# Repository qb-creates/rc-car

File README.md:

# RC Car Project
This project is a custom-built remote-controlled (RC) car, designed from the ground up with custom electronics, PCB design, and embedded firmware for both the car and its remote.

- Project Video (YouTube): https://youtu.be/qdBbDeDglmY
- Bidirectional Motor Driver (H-Bridge): https://en.wikipedia.org/wiki/H-bridge
- Steering Servo PWM Control: https://en.wikipedia.org/wiki/Servo_control
- nRF24L01 Wireless Transceiver Module: https://www.instructables.com/NRF24L01-Tutorial-Arduino-Wireless-Communication/

<div align="center">
	
</div>

## Table of Contents
1. [Software Used](#software)
2. [Drive and Steering Control Circuit](#driveandsteeringcircuit)
    - [RF Receiver](#rfreceiver)
    - [Steering Servo Control](#steering)
    - [Drive Motor Control](#drivemotor)
    - [Power Consumption](#powerconsumption)
    - [Charging Notes](#carcharging)
    - [Parts List](#carpartslist)
    - [Schematics](#carschematics)
    - [PCB Images](#carpcbimages)
3. [Remote Control Circuit](#remotecontrolcircuit)
    - [RF Transmitter](#rftransmitter)
    - [Control Input Processing](#controlinputprocessing)
        - [Throttle Input (Left Analog Stick)](#throttleprocessing)
        - [Steering Input (Right Analog Stick)](#steeringprocessing)
    - [Charging Notes](#remotecharging)
    - [Parts List](#remotepartslist)
    - [Schematics](#remoteschematics)
    - [PCB Images](#remotepcbimages)
4. [Pin Mapping](#pinmapping)
    - [Car Controller (ATmega164A)](#carpinmapping)
    - [Remote Controller (ATmega164A)](#remotepinmapping)
5. [STL Viewer](#stlviewer)
    - [Car Mechanical Mounts STL](#carmechanicalmountsstl)
    - [Controller Housing STL](#controllerhousingstl)

## 1. Software Used
- VSCode with PlatformIO extension: https://docs.platformio.org/en/latest/what-is-platformio.html
- AVRDUDE (Flash Uploader): https://github.com/avrdudes/avrdude
- KiCad (PCB Design): https://www.kicad.org
- Tinkercad (Controller and parts Design): https://www.tinkercad.com/

## 2. Drive and Steering Control Circuit
This board is the car's real-time control core. It receives wireless throttle/steering commands from the handheld transmitter, converts steering targets into stable hardware PWM for the MG90S servo, and drives the rear motor through a protected H-bridge path with direction dead-time and command deadbands for smoother behavior. The result is a compact control system designed for responsive handling, predictable failsafe behavior, and reliable power delivery under changing load.

<div align="center">
 <table>
     <tr>
         <td></td>
         <td></td>
     </tr>
     <tr>
         <td></td>
         <td></td>
     </tr>
 </table>
</div>

### RF Receiver
The car uses an nRF24L01+ module with the RF24 library over SPI to receive drive and steering commands from the handheld controller. In firmware, the radio object is created as `RF24 radio(CE_PIN, CSN_PIN)` with CE on PB0 and CSN on PB1.

The RF stack is configured in `configureRFRadio()` with:

- `radio.begin()` hardware check (halts if radio is not detected)
- `radio.setPALevel(RF24_PA_LOW)` to reduce TX power/current
- `radio.enableDynamicPayloads()`
- `radio.setAutoAck(false)`
- Pipe/address setup using `"jag-1"` and `"jag-2"`
- `radio.startListening()` so this node stays in RX mode

An important part of the RF path is Timer0 timing configuration. Because this firmware includes `#include <RF24.h>`, the RF24 stack depends on `millis()`/`micros()` timing for operations such as CE pulse timing, transmit timing windows, retry timing, and transaction spacing.

The RF24 library itself does not directly configure Timer0. Instead, those timing primitives are provided by the Arduino core (`millis()`/`micros()`), and the project sets Timer0 for a 50 us timing base:

```cpp
TCCR0A = (1 << COM0B1) | (1 << WGM01) | (1 << WGM00);
TCCR0B = (1 << WGM02) | (1 << CS01); // prescaler = 8
OCR0A = 49;
```

At 8 MHz CPU clock with prescaler 8:

- Timer clock = 8 MHz / 8 = 1 MHz
- Timer tick = 1 us
- Period = (49 + 1) x 1 us = 50 us

So the Timer0 event period is 50 us (20 kHz). Timer0 is intentionally kept running at this rate so the `millis()`/`micros()` time base used by RF24 remains available and stable.

The receiver expects a `MotorControlPayload` packet with two fields:

- `int16_t ocrMotor` for signed throttle/drive command
- `uint16_t ocrSteering` for servo pulse width command in microseconds

This payload is 4 bytes total (`2 + 2`), and after reception the car firmware applies it directly:

- `OCR1B = payload.ocrSteering` for steering position
- `payload.ocrMotor` drives H-bridge direction/speed logic with a deadband of -15 to +15

Reliability/safety behavior tied to RF reception:

- On first valid packet, watchdog is enabled (`WDTO_2S`)
- Each additional valid packet resets the watchdog
- If RF packets stop arriving, watchdog timeout forces a reset/failsafe

### Steering Servo Control
Steering is driven by an MG90S servo using Timer1 hardware PWM on OC1B (PD4). The car firmware configures Timer1 in Fast PWM mode 14 with ICR1 as TOP, prescaler = 8, and ICR1 = 20000. With an 8 MHz clock, that gives a 1 us timer tick and about a 50 Hz control period (20 ms), which matches standard hobby servo timing.

The commanded steering pulse is written directly to OCR1B. Steering values are transmitted as absolute pulse widths in microseconds. Instead of assuming a fixed joystick center, the controller now supports calibration by entering measured joystick potentiometer voltages for minimum, maximum, and center. Those measured values are used to map ADC input to the steering pulse range and produce a more accurate neutral point (typically near 1900 us). On the car side, OCR1B is updated from the payload each loop:

- Neutral: calibrated from measured joystick center voltage (typically ~1900 us)
- Left/Right command range: ~1520 us to ~2280 us
- PWM period: ~20 ms (50 Hz)
- Steering deadzone: +/-90 us around calibrated center snaps to neutral to reduce twitch

This keeps steering response deterministic because the servo waveform is generated in hardware (Timer1), not by software toggling.

### Drive Motor Control
The drive motor uses a discrete H-bridge driven by a hybrid approach: latch lines select direction, while PWM is generated in software via Timer2 interrupts.

H-bridge signal assignment:

- PC0: Forward latch
- PC1: Forward PWM
- PC2: Reverse latch
- PC3: Reverse PWM

Timer2 is configured for Fast PWM with OCR2A as TOP. With OCR2A = 199 and prescaler = 8 at 8 MHz, PWM frequency is about 5 kHz. Instead of using OC2A/OC2B output pins directly, compare interrupts are used:

- TIMER2_COMPA_vect sets the active direction PWM pin high (PC1 for forward or PC3 for reverse)
- TIMER2_COMPB_vect clears that same active pin low

This effectively creates direction-dependent PWM on one of two output pins while the opposite side remains off.

Direction changes are intentionally staged to protect the bridge and drivetrain:

1. Disable Timer2 PWM (stop switching)
2. Force all H-bridge outputs low
3. Wait 150 ms dead-time
4. Assert new direction latch (PC0 forward or PC2 reverse)
5. Re-enable Timer2 PWM

That delay prevents hard instant reversals and helps ensure MOSFETs on the same side of the H-bridge are not on at the same time during direction transitions, reducing shoot-through/braking stress.

Additional control logic from the car firmware:

- Speed deadband: commands between -15 and +15 stop the motor to avoid joystick/noise creep
- Steering deadzone: commands within +/-90 us of the calibrated center are snapped to neutral
- Direction is only changed when needed (or from stopped state)
- A watchdog is enabled after first RF packet and reset on each valid packet; if RF traffic is lost, the MCU resets after the watchdog timeout (2 s)

### Why RF reception is harder with this PWM approach
Using Timer2 compare interrupts for every PWM cycle means the MCU is servicing frequent interrupts continuously while also polling and reading nRF24 payloads over SPI. That interrupt load can steal time from RF handling and make robust payload reception harder than a pure hardware-PWM motor path.

In practice, the current tuning (about 5 kHz PWM, deadband around zero, staged direction changes) was a workable sweet spot between motor smoothness and reliable radio updates. A strictly hardware PWM implementation for both drive channels would reduce ISR overhead and leave more CPU time for RF processing.

### Power Consumption
This power system was sized around worst-case drive events (motor stall plus active steering), not just average cruising current.

Estimated load envelope:

- 9V drive motor stall current at 7.2V: ~600 mA
- MG90S steering servo working current: ~600-700 mA
- Control circuitry (MCU, RF, logic, support electronics): ~20 mA

Worst-case instantaneous estimate:

- Total peak demand: $0.60 + 0.70 + 0.02 \approx 1.32\,A$

Battery capability:

- 2S 200 mAh pack, 20C rating
- Maximum continuous supply: $0.2\,Ah \times 20 = 4\,A$

Power-stage device headroom:

- IRLML6244 continuous drain current: 6.3 A (comfortably above motor stall current)
- IRLML2246 continuous source current: -1.3 A (above the ~600 mA motor stall requirement in this bridge path)

Conclusion: the battery and MOSFET current limits provide practical headroom over the expected peak load, so the system can supply drive, steering, and control electronics simultaneously under normal and transient operation.

### Charging Notes
For safe charging practice on the car side, do not charge the car while it is powered on. Turn the car off first, then connect the charger.

---
### Parts List
<div align="center">
    <table>
        <tr>
            <td valign="top">
                <table>
                    <tr><th>Part Number</th><th>Quantity</th></tr>
                    <tr><td><a href="https://www.digikey.com/en/products/detail/rubycon/25YXG220MEFC6-3X11/3134189">220uF Capacitor</a></td><td align="center">x1</td></tr>
                    <tr><td><a href="https://www.digikey.com/en/products/detail/taiyo-yuden/TMK107B7105KA-T/2714162">1uF Capacitor</a></td><td align="center">x2</td></tr>
                    <tr><td><a href="https://www.digikey.com/en/products/detail/samsung-electro-mechanics/CL21A106KAYNNNG/3894413">10uF Capacitor</a></td><td align="center">x1</td></tr>
                    <tr><td><a href="https://www.digikey.com/en/products/detail/murata-electronics/GRM188R61E225KA12D/4905349">2.2uF Capacitor</a></td><td align="center">x1</td></tr>
                    <tr><td><a href="https://www.digikey.com/en/products/detail/kemet/C0603C104K3RACTU/416044">.1uF Capacitor</a></td><td align="center">x4</td></tr>
                    <tr><td><a href="https://www.digikey.com/en/products/detail/venkel/CTL1206FRD1T/13245061">LED</a></td><td align="center">x1</td></tr>
                    <tr><td><a href="https://www.digikey.com/en/products/detail/diodes-incorporated/1N5819HW-7-F/814970">1N5819HW-7-F Diode</a></td><td align="center">x4</td></tr>
                    <tr><td><a href="https://www.amazon.com/2-54mm-Breakaway-Female-Connector-Arduino/dp/B01MQ48T2V/ref=sr_1_2_sspa?crid=37UI1XQQ1YOGK&dib=eyJ2IjoiMSJ9.dQRG7A390Cr7G0eECwl3ySotcaXfI28I1uUKHcmiPHf-hvTrpk4-mLxeOfBP_o2wgeNP09ah4l4Z_nh4K_ky6uhpN37tS8i2I8bk7hElYNXx-FAMr_ipA9P94e9JhgRABouD4lHJnLV6bc2VHVILnmQpPnT6LynWmghNohKPKs16E5RMkmBnBZLmoQyECbt8tk0IWHyfDAvT8Id0p6m7HikZdiL1Mb9oZ9zR8lDkjQg.dCZRPJ_88iquw6HqnK28jkzvtgYozecW_lBzuIykXWo&dib_tag=se&keywords=header%2Bpins&qid=1778354973&sprefix=header%2Bpins%2Caps%2C146&sr=8-2-spons&sp_csd=d2lkZ2V0TmFtZT1zcF9hdGY&th=1">Header Pins</a></td><td align="center">x17</td></tr>
                    <tr><td><a href="https://www.digikey.com/en/products/detail/onsemi/MMBT3904LT1G/919601">MMBT3904</a></td><td align="center">x2</td></tr>
                    <tr><td><a href="https://www.digikey.com/en/products/detail/umw/UMWIRLML2246TR/24889419">IRLML2246 / UMWIRLML2246TR</a></td><td align="center">x2</td></tr>
                    <tr><td><a href="https://www.digikey.com/en/products/detail/infineon-technologies/IRLML6244TRPBF/2393871">IRLML6244</a></td><td align="center">x2</td></tr>
                    <tr><td><a href="https://www.digikey.com/en/products/detail/stackpole-electronics-inc/RMCF0603FT470K/1761140">470k ohm Resistor</a></td><td align="center">x1</td></tr>
                    <tr><td><a href="https://www.digikey.com/en/products/detail/yageo/RC0603JR-07510KL/726802">500k ohm Resistor</a></td><td align="center">x1</td></tr>
                    <tr><td><a href="https://www.digikey.com/en/products/detail/koa-speer-electronics-inc/RK73B1JTTD154J/9844780">150k ohm Resistor</a></td><td align="center">x1</td></tr>
                    <tr><td><a href="https://www.digikey.com/en/products/detail/yageo/RC0603JR-071K5L/726689">1.5k ohm Resistor</a></td><td align="center">x1</td></tr>
                    <tr><td><a href="https://www.digikey.com/en/products/detail/stackpole-electronics-inc/RMCF0603JT10K0/1758104">10k ohm Resistor</a></td><td align="center">x5</td></tr>
                </table>
            </td>
            <td width="24"></td>
            <td valign="top">
                <table>
                    <tr><th>Part Number</th><th>Quantity</th></tr>
                    <tr><td><a href="https://www.digikey.com/en/products/detail/yageo/RC0603JR-071K3L/726686">1.3k ohm Resistor</a></td><td align="center">x4</td></tr>
                    <tr><td><a href="https://www.digikey.com/en/products/detail/stackpole-electronics-inc/RMCF0603FT10R0/1761152">10 ohm Resistor</a></td><td align="center">x2</td></tr>
                    <tr><td><a href="https://www.digikey.com/en/products/detail/omron-electronics-inc-emc-div/A6S-1104-PH/3102847">SW_SPST</a></td><td align="center">x1</td></tr>
                    <tr><td><a href="https://www.digikey.com/en/products/detail/texas-instruments/TPS3840DL35DBVR/15857118">TPS3840</a></td><td align="center">x1</td></tr>
                    <tr><td><a href="https://www.digikey.com/en/products/detail/microchip-technology/MIC3975-5-0YMM-TR/1029778">MIC3975-5.0YMM Voltage Regulator</a></td><td align="center">x1</td></tr>
                    <tr><td><a href="https://www.digikey.com/en/products/detail/microchip-technology/MIC5225-3-3YM5-TR/1815447">MIC5225-3.3YM5 Voltage Regulator</a></td><td align="center">x1</td></tr>
                    <tr><td><a href="https://www.digikey.com/en/products/detail/microchip-technology/ATMEGA164A-AU/2271202">ATmega164A-A</a></td><td align="center">x1</td></tr>
                    <tr><td><a href="https://www.amazon.com/dp/B0BWJ4RKGV?ref=ppx_yo2ov_dt_b_fed_asin_title">MG90S servo motor</a></td><td align="center">x1</td></tr>
                    <tr><td><a href="https://www.amazon.com/uxcell-Micro-11500-12000RPM-Remote-Control/dp/B07M99JK6Y/ref=sr_1_6_pp?crid=15ZR5I0IA9JJI&dib=eyJ2IjoiMSJ9.0dTLxilAb6xq-6TUjWUHu4LHY67tPVw3OW_p63iFn0nxHTF8tJOEU3O_Cb8oOwE6WxJZW0BjBXIf0G8GfpGx34Xib0qnggH2QTWBRLxwTrt1dVHrFBr4m3qlymM1dp_HGhddBT5o2u24L-f4An4mHsWxuHhcwAWkuWetTyXovK-j6vw5tc8bw8An9Jwehol9gVoWqmTKBzJJhRpDE5yd1FT2j8fYInDLiEd9pn63in9N35NYOYHjUvUYXkuJJkr2DH7aythkyAL53UUCrgou9nhxGCkFBAQQLPBe2CI7QtI.hByQYkM03NWvQAiFiiVJo0fbgudInFzwV0ohKh8QIlI&dib_tag=se&keywords=9v+motor&qid=1778356523&sprefix=9v+motor%2Caps%2C163&sr=8-6">9V DC Motor</a></td><td align="center">x1</td></tr>
                    <tr><td><a href="https://www.amazon.com/KiNSMART-Jaguar-Project-Metal-Model/dp/B0GXDP3B83/ref=sr_1_2?crid=HY25IPNV0BHN&dib=eyJ2IjoiMSJ9.kNHmPeKKto7l4mN5kOvqBU7R0Xlsnn2LHCeKZya09DTJalbcDjd4JoTcYEG4oBi7Ljllb7X6_TGZSaIGPy1Xm1sebzbI1yp2mHZeyxYMDKpjf4Jqk94GJpw4gnU1N_5tkqw1yrXIqMnX5ZyADOEFBC7UcSktNJJQAYE5tSmkBo9atjGda3yxCk-vgOEnLoZFFx2acgDjpZFOOCdXU92NyMzapczCn7FhwygMaJ_Cei5oG747OONrkMHwEvzIolQ_2xz7kVeILcwJkr2IywmRw9VX98jR5jMxBVIL_H83mhw.naunVJhW78f1ztCTSTYnX7RhDgAuPRFgKA2PJmHRRKo&dib_tag=se&keywords=kinsmart%2B1%3A38&qid=1779063547&sprefix=kinsmart%2B1%2B38%2Caps%2C216&sr=8-2&th=1">Kinsmart Jaguar 1:38</a></td><td align="center">x1</td></tr>
                    <tr><td><a href="https://www.amazon.com/HiLetgo-NRF24L01-Wireless-Transceiver-Module/dp/B00LX47OCY/ref=sr_1_1_sspa?crid=1USO9UOFDEZL5&dib=eyJ2IjoiMSJ9.HpGu4TebgrLEY6IjfmGnCKONGE1zifAy342llWfR4vcsJ4_OTj71wcfjuLFi42g9LnfOsZybnBvz4HCtPFZh7IoO0VCtoV4SHTwJkmzj3SyTmBWTWfYEwK0bZ-6KAhnJqpXuroU3ExNMIQ_0sb6zAw01BAymwhYK7jVncUvl8YxZV7HAVItE-ISceLL5caDSPRu-nl4dzw8eF-t1VvKSdHE_Pz68YolGVn5D4_TDIAE.6OIyGVxp3k88Grsb6QKkfbgzYiEAVdqjkrvRE4yyM6M&dib_tag=se&keywords=nrf24l01&qid=1778356552&sprefix=nrf%2Caps%2C232&sr=8-1-spons&sp_csd=d2lkZ2V0TmFtZT1zcF9hdGY&psc=1">NRF24L01+ Module</a></td><td align="center">x1</td></tr>
                    <tr><td><a href="https://www.amazon.com/dp/B07MW2L96L?ref=ppx_yo2ov_dt_b_fed_asin_title">7.4V battery</a></td><td align="center">x1</td></tr>
                    <tr><td><a href="https://www.amazon.com/200PCS-Module-Plastic-Single-Spindle/dp/B0DKHG96PL/ref=sr_1_6?crid=W0RZLTTF36ZV&dib=eyJ2IjoiMSJ9.rd3Q4coQN-xK_iVME0RsSWQTjAsKta_V4h4vm12weDUJC74fnjatzucJO07yHtkLeIzfxeMC2dxmPiht58xboKdyTAKydnddtAAmDD_aARQfSeJf72BiNVGOLvJEh9z4o6wPQQIsW7IFXJZAsVFzRvb3aBc2lONKzi84gw8UxRRc2rQ9rWUQvz_yelBZoDNSvcFoSqvusfdJFjuKQ47WFcnAPOwQnc2LdEzRRlFGYalz5QPsVB-hWhAqh67OA6riZCc13JSazX8bvwV50yC13BdBVPq8QEGZLQo3CGB_GXM.rLefd6TJ3JQPyoYEO4myNas1mQIUsuXzyBHIw13Vpyw&dib_tag=se&keywords=dc%2Bmotor%2Bgears&qid=1778804461&sprefix=dc%2Bmotor%2Bgear%2Caps%2C142&sr=8-6&th=1">Gears</a></td><td align="center">x1</td></tr>
                    <tr><td><a href="https://www.amazon.com/ruthex-Threaded-Insert-pieces-ultrasound/dp/B088QJG676/ref=sr_1_3?crid=327WC4A3U357H&dib=eyJ2IjoiMSJ9.v_Af1Sv2DMXyynp1rO3uN2cjI_LkHpW2Xd3NuL9RUn1yz2Ym6BTHo47Bnvh-mF3rih3MIxPZyDCFRwN3f8bgTgfOqS-2FD8o-WWmIpuq7XJIrvCSKP6iwhtXO1FB6g2J8vFhgMjuaMVbjKPUpn3U8iuk4FPTnzt9IQcKtjUuxKiJM3PQJf3MPDf15V62fIp3_oibwlJtUKJ7oyWbckn9BPgwhhw0z9gTb7ylLCQjULA.KUBGIt58ag9IJXW2aWAnvHSlQ59y6f_kavaLpQD422E&dib_tag=se&keywords=inserts%2Bm2&qid=1778806075&sprefix=inserts%2Bm%2Caps%2C197&sr=8-3&th=1">M2 Inserts</a></td><td align="center">x3</td></tr>
                    <tr><td><a href="https://www.amazon.com/Phillips-Countersunk-Electronic-Accessories-Samsung/dp/B07HC3LQYS/ref=sr_1_8?crid=2ISFEC45EBS5Q&dib=eyJ2IjoiMSJ9.sToeJ_cHiwrPYQ_C9rq2gwq_BqFxCk_dAqNz8qbKlTKQla66SuHvAVoMEMQE3FrKbT_cXuKk3EDQL7eTiH6WYWt4xdVsIXdoV99uXBCs7qfK_HdB1wotMUmIz4MZM-fYqvCkvNTV6tpBtMOlWfMOOT3xG69H9dmbPd9TCbIKidT_fAgNMZEY2BR0qPmHW3JfhP0KSYKgUQ9dyiHrulr41WxGtIHFVkrdDqeaHCOoUuo.r_V_du0eyowAqg1oQ__QllHDwAeUxV1av7Z4HFjVBKw&dib_tag=se&keywords=m2%2Bscrews&qid=1778806119&sprefix=m2%2Bscrew%2Caps%2C149&sr=8-8&th=1">M2 screws</a></td><td align="center">x3</td></tr>
                </table>
            </td>
        </tr>
    </table>
</div>

### Schematics
<div align="center">
    
</div>

### PCB Images
<div align="center">
 <table>
     <tr>
         <td></td>
         <td></td>
     </tr>
     <tr>
         <td></td>
         <td></td>
     </tr>
 </table>
</div>

## 3. Remote Control Circuit
The handheld controller samples two joystick axes, converts them into throttle and steering commands, and transmits those values over 2.4 GHz to the car at a steady update rate. The design goal is low-latency control with stable center behavior so the car tracks driver input without twitching or drift.

<div align="center">
 <table>
     <tr>
         <td></td>
         <td></td>
     </tr>
     <tr>
         <td></td>
         <td></td>
     </tr>
 </table>
</div>

### RF Transmitter
The remote uses an nRF24L01+ module with RF24 over SPI to transmit `MotorControlPayload` packets containing `ocrMotor` and `ocrSteering`. During initialization, firmware performs a radio hardware check, configures dynamic payload mode, and sets TX/RX addresses for the paired node. Timer0 is also configured with a 50 us base so the `millis()`/`micros()` timing used by RF24 remains stable while packets are sent continuously.

### Control Input Processing
Joystick values are read through the ADC and mapped into the exact command domains expected by the vehicle firmware. This preprocessing keeps control semantics consistent across the RF link: signed throttle around zero and steering in absolute pulse-width units centered at a calibrated neutral.

#### Throttle Input (Left Analog Stick)
Throttle is sampled on ADC channel 0, inverted to match intuitive stick direction, scaled into a signed drive command, and centered around zero. Positive values represent forward demand, negative values represent reverse demand, and near-zero commands cooperate with the car-side deadband to prevent idle creep.

#### Steering Input (Right Analog Stick)
Steering is sampled on ADC channel 1 and converted using a calibration profile where measured joystick potentiometer minimum, maximum, and center voltages are entered in firmware. The mapping uses those measured endpoints and center value to generate steering pulses, then clamps to the valid steering window before transmission. This makes neutral alignment and left/right travel more accurate than a fixed center assumption. A center deadzone is applied so small stick jitter and ADC noise snap back to neutral, reducing servo chatter and improving straight-line stability.

To measure and enter steering calibration voltages:

1. Power the controller on.
2. Connect the multimeter to ground and to the X-axis test point by the left controller.
3. Measure the voltage with the analog stick in its center position (center voltage).
4. Measure the voltage with the stick moved all the way to the right (minimum voltage for this mapping).
5. Measure the voltage with the stick moved all the way to the left (maximum voltage for this mapping).

### Charging Notes
The remote has a built-in LiPo charging circuit. When a charger is connected, the controller may automatically power on while charging. You can place the power switch in the OFF position before charging if you prefer it to stay off.

---
### Parts List
<div align="center">
    <table>
        <tr>
            <td valign="top">
                <table>
                    <tr><th>Part Number</th><th>Quantity</th></tr>
                    <tr><td><a href="https://www.digikey.com/en/products/detail/jst-sales-america-inc/S2B-PH-SM4-TB/926655">JST Connector</a></td><td align="center">x1</td></tr>
                    <tr><td><a href="https://www.digikey.com/en/products/detail/samsung-electro-mechanics/CL10A475KP8NNNC/3886702">4.7uF Capacitor</a></td><td align="center">x2</td></tr>
                    <tr><td><a href="https://www.digikey.com/en/products/detail/taiyo-yuden/TMK107B7105KA-T/2714162">1uF Capacitor</a></td><td align="center">x2</td></tr>
                    <tr><td><a href="https://www.digikey.com/en/products/detail/murata-electronics/GRM188R61E225KA12D/4905349">2.2uF Capacitor</a></td><td align="center">x1</td></tr>
                    <tr><td><a href="https://www.digikey.com/en/products/detail/kemet/C0603C104K3RACTU/416044">.1uF Capacitor</a></td><td align="center">x4</td></tr>
                    <tr><td><a href="https://www.digikey.com/en/products/detail/venkel/CTL1206FRD1T/13245061">LED</a></td><td align="center">x2</td></tr>
                    <tr><td><a href="https://www.digikey.com/en/products/detail/gct/USB4125-GF-A/13547384">USB_C_Receptacle_USB2.0_14P</a></td><td align="center">x1</td></tr>
                    <tr><td><a href="https://www.digikey.com/en/products/detail/w-rth-elektronik/61201021621/2060590?gclsrc=aw.ds&gad_source=1&gad_campaignid=20234014242&gbraid=0AAAAADrbLliydMvIIXJNX99D3SyONNFow&gclid=CjwKCAjwtvvPBhBuEiwAPMijr9iKDJDvfxlLCPFpasA9r130lziQwH1Oz1Nx0EE10dvVf4E5pzsRdxoCSPkQAvD_BwE">AVR-ISP-10</a></td><td align="center">x1</td></tr>
                    <tr><td><a href="https://www.amazon.com/2-54mm-Breakaway-Female-Connector-Arduino/dp/B01MQ48T2V/ref=sr_1_2_sspa?crid=37UI1XQQ1YOGK&dib=eyJ2IjoiMSJ9.dQRG7A390Cr7G0eECwl3ySotcaXfI28I1uUKHcmiPHf-hvTrpk4-mLxeOfBP_o2wgeNP09ah4l4Z_nh4K_ky6uhpN37tS8i2I8bk7hElYNXx-FAMr_ipA9P94e9JhgRABouD4lHJnLV6bc2VHVILnmQpPnT6LynWmghNohKPKs16E5RMkmBnBZLmoQyECbt8tk0IWHyfDAvT8Id0p6m7HikZdiL1Mb9oZ9zR8lDkjQg.dCZRPJ_88iquw6HqnK28jkzvtgYozecW_lBzuIykXWo&dib_tag=se&keywords=header%2Bpins&qid=1778354973&sprefix=header%2Bpins%2Caps%2C146&sr=8-2-spons&sp_csd=d2lkZ2V0TmFtZT1zcF9hdGY&th=1">nRF24L01+ Headers</a></td><td align="center">x1</td></tr>
                    <tr><td><a href="https://www.amazon.com/Automation-Joysticks-Compatible-Controllers-Precision/dp/B09Y2R1GLV">Joystick B09Y2R1GLV</a></td><td align="center">x2</td></tr>
                    <tr><td><a href="https://www.digikey.com/en/products/detail/infineon-technologies/IRLML6244TRPBF/2393871">IRLML6244</a></td><td align="center">x1</td></tr>
                    <tr><td><a href="https://www.digikey.com/en/products/detail/yageo/RC0603FR-075K1L/727268">5.1k ohm Resistor</a></td><td align="center">x2</td></tr>
                    <tr><td><a href="https://www.digikey.com/en/products/detail/koa-speer-electronics-inc/RK73B1JTTD154J/9844780">150k ohm Resistor</a></td><td align="center">x1</td></tr>
                </table>
            </td>
            <td width="24"></td>
            <td valign="top">
                <table>
                    <tr><th>Part Number</th><th>Quantity</th></tr>
                    <tr><td><a href="https://www.digikey.com/en/products/detail/yageo/RC0603JR-071K5L/726689">1.5k ohm Resistor</a></td><td align="center">x1</td></tr>
                    <tr><td><a href="https://www.digikey.com/en/products/detail/stackpole-electronics-inc/RMCF0603JT10K0/1758104">10k ohm Resistor</a></td><td align="center">x2</td></tr>
                    <tr><td><a href="https://www.digikey.com/en/products/detail/yageo/RC0603FR-07330RL/727162">330 ohm Resistor</a></td><td align="center">x1</td></tr>
                    <tr><td><a href="https://www.digikey.com/en/products/detail/yageo/RC0603JR-071K3L/726686">1.3k ohm Resistor</a></td><td align="center">x1</td></tr>
                    <tr><td><a href="https://www.digikey.com/en/products/detail/omron-electronics-inc-emc-div/A6S-1104-PH/3102847">SW_SPST</a></td><td align="center">x1</td></tr>
                    <tr><td><a href="https://www.digikey.com/en/products/detail/texas-instruments/TPS3840DL35DBVR/15857118">TPS3840</a></td><td align="center">x1</td></tr>
                    <tr><td><a href="https://www.digikey.com/en/products/detail/microchip-technology/MCP73831T-4ADI-OT/1874437?gclsrc=aw.ds&gad_source=1&gad_campaignid=20790518593&gbraid=0AAAAADrbLlgvRBylAxpp-GjrKMif8Czig&gclid=CjwKCAjwtvvPBhBuEiwAPMijr3YD6e-gwd-PDBrTAI6AF4DaDnOhNqFPZpuGwQkKEnNPv-7e_AYXQRoCGHgQAvD_BwE">MCP73831-2-OT</a></td><td align="center">x1</td></tr>
                    <tr><td><a href="https://www.digikey.com/en/products/detail/microchip-technology/MIC5225-3-3YM5-TR/1815447">MIC5225-3.3YM5 Voltage Regulator</a></td><td align="center">x1</td></tr>
                    <tr><td><a href="https://www.digikey.com/en/products/detail/microchip-technology/ATMEGA164A-AU/2271202">ATmega164A-A</a></td><td align="center">x1</td></tr>
                    <tr><td><a href="https://www.amazon.com/HiLetgo-NRF24L01-Wireless-Transceiver-Module/dp/B00LX47OCY/ref=sr_1_1_sspa?crid=1USO9UOFDEZL5&dib=eyJ2IjoiMSJ9.HpGu4TebgrLEY6IjfmGnCKONGE1zifAy342llWfR4vcsJ4_OTj71wcfjuLFi42g9LnfOsZybnBvz4HCtPFZh7IoO0VCtoV4SHTwJkmzj3SyTmBWTWfYEwK0bZ-6KAhnJqpXuroU3ExNMIQ_0sb6zAw01BAymwhYK7jVncUvl8YxZV7HAVItE-ISceLL5caDSPRu-nl4dzw8eF-t1VvKSdHE_Pz68YolGVn5D4_TDIAE.6OIyGVxp3k88Grsb6QKkfbgzYiEAVdqjkrvRE4yyM6M&dib_tag=se&keywords=nrf24l01&qid=1778356552&sprefix=nrf%2Caps%2C232&sr=8-1-spons&sp_csd=d2lkZ2V0TmFtZT1zcF9hdGY&psc=1">NRF24L01+ Module</a></td><td align="center">x1</td></tr>
                    <tr><td><a href="https://www.amazon.com/EEMB-Rechargeable-Connector-Parrott-Polarity/dp/B0B7R8CS2C/ref=sr_1_9?crid=2PNJXHT8O2BD7&dib=eyJ2IjoiMSJ9.ytY0ATgoZUTp8fkKfIbFwxfJ-RPFGOh8Fljs3SALwOdc0E5um9MqwU3Nf561TyqW5eWp_bfODQRFYKAYV0HQlPTNrv5PexF4DVU2RbBdxKcuSmBcDQuw5ImA3T8MQCieUYtHxHjlPQKIey3tmjioRLIZljCtEmJfrXf2yw62FtfaherhM4QZP-lGmU_qZ4IiXu3H0jwThQ-BqoBcTMGELR8DD_BVenflcsgEmfo4edXbIZRGZtWTI9cXMjF2NkhywL7GquoxWDFoC_LZDs7lVysMe3o4p0KdNnO_wNiqgRM.z8oLo5uD7M9zWKGX-XX1qytnO6Q6kw132uBizXV_u2c&dib_tag=se&keywords=250ma+hour+lipo+battery&qid=1779063612&sprefix=250ma+hour+lipo+battery%2Caps%2C142&sr=8-9">3.7v battery</a></td><td align="center">x1</td></tr>
                    <tr><td><a href="https://www.amazon.com/ruthex-Threaded-Insert-pieces-ultrasound/dp/B088QJG676/ref=sr_1_3?crid=327WC4A3U357H&dib=eyJ2IjoiMSJ9.v_Af1Sv2DMXyynp1rO3uN2cjI_LkHpW2Xd3NuL9RUn1yz2Ym6BTHo47Bnvh-mF3rih3MIxPZyDCFRwN3f8bgTgfOqS-2FD8o-WWmIpuq7XJIrvCSKP6iwhtXO1FB6g2J8vFhgMjuaMVbjKPUpn3U8iuk4FPTnzt9IQcKtjUuxKiJM3PQJf3MPDf15V62fIp3_oibwlJtUKJ7oyWbckn9BPgwhhw0z9gTb7ylLCQjULA.KUBGIt58ag9IJXW2aWAnvHSlQ59y6f_kavaLpQD422E&dib_tag=se&keywords=inserts%2Bm2&qid=1778806075&sprefix=inserts%2Bm%2Caps%2C197&sr=8-3&th=1">M2 Inserts</a></td><td align="center">x10</td></tr>
                    <tr><td><a href="https://www.amazon.com/Phillips-Countersunk-Electronic-Accessories-Samsung/dp/B07HC3LQYS/ref=sr_1_8?crid=2ISFEC45EBS5Q&dib=eyJ2IjoiMSJ9.sToeJ_cHiwrPYQ_C9rq2gwq_BqFxCk_dAqNz8qbKlTKQla66SuHvAVoMEMQE3FrKbT_cXuKk3EDQL7eTiH6WYWt4xdVsIXdoV99uXBCs7qfK_HdB1wotMUmIz4MZM-fYqvCkvNTV6tpBtMOlWfMOOT3xG69H9dmbPd9TCbIKidT_fAgNMZEY2BR0qPmHW3JfhP0KSYKgUQ9dyiHrulr41WxGtIHFVkrdDqeaHCOoUuo.r_V_du0eyowAqg1oQ__QllHDwAeUxV1av7Z4HFjVBKw&dib_tag=se&keywords=m2%2Bscrews&qid=1778806119&sprefix=m2%2Bscrew%2Caps%2C149&sr=8-8&th=1">M2 Screws</a></td><td align="center">x10</td></tr>
                </table>
            </td>
        </tr>
    </table>
</div>

### Schematics
<div align="center">
    
</div>

### PCB Images
<div align="center">
 <table>
     <tr>
         <td></td>
         <td></td>
     </tr>
     <tr>
         <td></td>
         <td></td>
     </tr>
 </table>
</div>

## 4. Pin Mapping 
ATmega164A/P pin information is from the Microchip datasheet: https://ww1.microchip.com/downloads/en/devicedoc/atmel-8272-8-bit-avr-microcontroller-atmega164a_pa-324a_pa-644a_pa-1284_p_datasheet.pdf

### Car Controller (ATmega164A)
| Signal | MCU Pin | Notes |
|:--|:--|:--|
| nRF24 CE | PB0 | Defined as `CE_PIN 0` in car RF firmware |
| nRF24 CSN | PB1 | Defined as `CSN_PIN 1` in car RF firmware |
| nRF24 SPI SCK | PB7 | Hardware SPI clock |
| nRF24 SPI MISO | PB6 | Hardware SPI MISO |
| nRF24 SPI MOSI | PB5 | Hardware SPI MOSI |
| nRF24 SPI SS | PB4 | Hardware SPI SS |
| Steering PWM (OC1B) | PD4 | Servo output (Timer1 OC1B) |
| Motor Forward Latch | PC0 | H-bridge control |
| Motor Forward PWM | PC1 | H-bridge control |
| Motor Reverse Latch | PC2 | H-bridge control |
| Motor Reverse PWM | PC3 | H-bridge control |
| Status LED | PD5 | Set during startup/status |

### Remote Controller (ATmega164A)
| Signal | MCU Pin | Notes |
|:--|:--|:--|
| nRF24 CE | PB0 | Defined as `CE_PIN 0` in remote RF firmware |
| nRF24 CSN | PB1 | Defined as `CSN_PIN 1` in remote RF firmware |
| nRF24 SPI SCK | PB7 | Hardware SPI clock |
| nRF24 SPI MISO | PB6 | Hardware SPI MISO |
| nRF24 SPI MOSI | PB5 | Hardware SPI MOSI |
| nRF24 SPI SS | PB4 | Hardware SPI SS |
| Throttle Joystick (Y) ADC | PA0 / ADC0 | Read with `readADC(0)` |
| Steering Joystick (X) ADC | PA1 / ADC1 | Read with `readADC(1)` |

## 5. STL Viewer 
### Car Mechanical Mounts STL 
- [Car Parts.stl](3d%20print/Car%20Parts.stl)

### Controller Housing STL 
- [Controller.stl](3d%20print/Controller.stl)

---

## License
See [LICENSE](LICENSE) for details.

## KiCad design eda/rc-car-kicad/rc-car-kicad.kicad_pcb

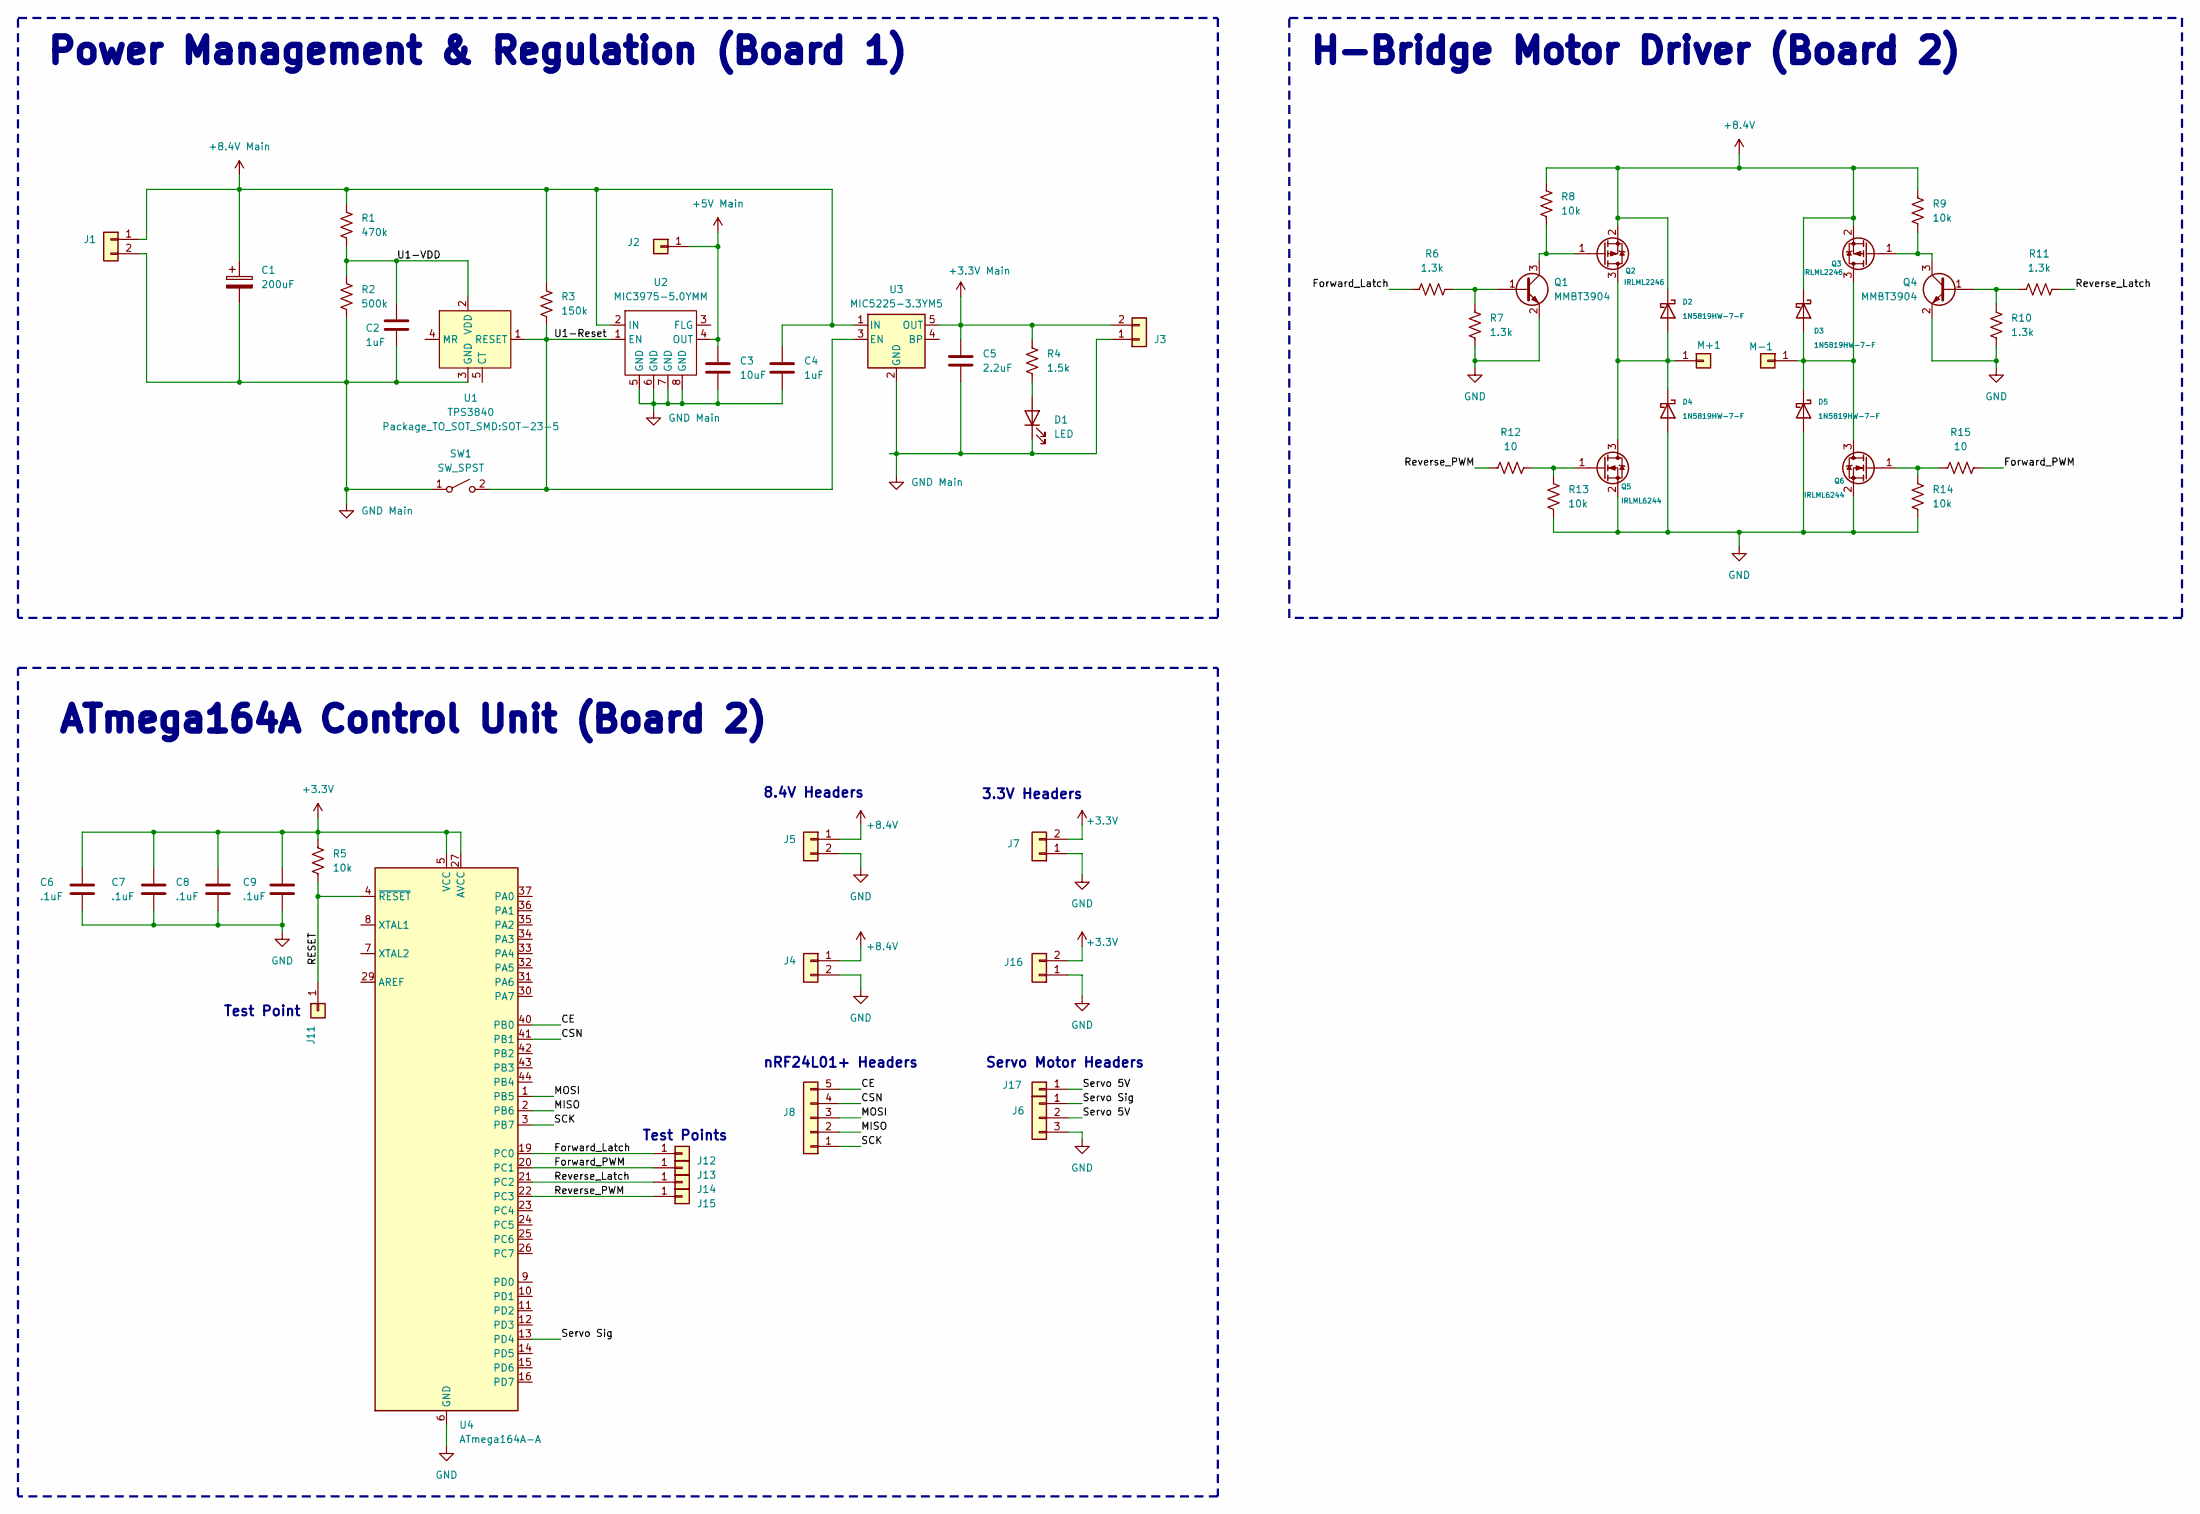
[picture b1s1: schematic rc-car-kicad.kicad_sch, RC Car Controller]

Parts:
C1: 200uF; CP_Radial_D6.3mm_P2.50mm
C2, C4: 1uF; C_0603_1608Metric_Pad1.08x0.95mm_HandSolder
C3: 10uF; C_0805_2012Metric_Pad1.18x1.45mm_HandSolder
C5: 2.2uF; C_0603_1608Metric_Pad1.08x0.95mm_HandSolder
C6, C7, C8, C9: .1uF; C_0603_1608Metric_Pad1.08x0.95mm_HandSolder
D1: LED; LED_1206_3216Metric
D2, D3, D4, D5: 1N5819HW-7-F; D_SOD-123
J1, J3: PinSocket_1x02_P2.54mm_Vertical
J2: PinSocket_1x01_P2.54mm_Vertical
J4, J5: PinHeader_1x02_P2.54mm_Vertical
J6: PinHeader_1x03_P2.54mm_Vertical
J7, J16: PinHeader_1x02_P2.54mm_Vertical_No_Courtyard
J8: PinHeader_1x05_P2.54mm_Vertical
J11: TestPoint_Pad_1.0x1.0mm
J12, J13, J14, J15: TestPoint_Pad_D1.0mm
J17: PinHeader_1x01_P2.54mm_Vertical
M+1: TestPoint_Pad_2.0x2.0mm
M-1: TestPoint_Pad_2.0x2.0mm
Q1, Q4: MMBT3904; SOT-23
Q2, Q3: IRLML2246; SOT-23
Q5, Q6: IRLML6244; SOT-23
R1: 470k; R_0603_1608Metric_Pad0.98x0.95mm_HandSolder
R2: 500k; R_0603_1608Metric_Pad0.98x0.95mm_HandSolder
R3: 150k; R_0603_1608Metric_Pad0.98x0.95mm_HandSolder
R4: 1.5k; R_0603_1608Metric_Pad0.98x0.95mm_HandSolder
R5, R8, R9, R13, R14: 10k; R_0603_1608Metric_Pad0.98x0.95mm_HandSolder
R6, R7, R10, R11: 1.3k; R_0603_1608Metric_Pad0.98x0.95mm_HandSolder
R12, R15: 10; R_0603_1608Metric_Pad0.98x0.95mm_HandSolder
SW1: SW_SPST; SW_DIP_SPSTx01_Slide_Omron_A6S-110x_W8.9mm_P2.54mm
U1: TPS3840; SOT-23-5
U2: MIC3975-5.0YMM; MSOP-8_3x3mm_P0.65mm
U3: MIC5225-3.3YM5; SOT-23-5
U4: ATmega164A-A; TQFP-44_10x10mm_P0.8mm

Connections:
+3.3V: C6.1, C7.1, C8.1, C9.1, J7.2, J16.2, R5.1, U4.5 (VCC), U4.17 (VCC), U4.27 (AVCC), U4.38 (VCC)
+3.3V Main: C5.1, J3.2, R4.2, U3.5 (OUT)
+5V Main: C3.1, J2.1, U2.4 (OUT)
+8.4V: D2.1 (K), D3.1 (K), J4.1, J5.1, Q2.2 (S), Q3.2 (S), R8.1, R9.1
+8.4V Main: C1.1, C4.1, J1.1, R1.1, R3.1, U2.2 (IN), U3.1 (IN)
/CE: J8.5, U4.40 (PB0)
/CSN: J8.4, U4.41 (PB1)
/Forward_Latch: J12.1, R6.1, U4.19 (PC0)
/Forward_PWM: J13.1, R15.2, U4.20 (PC1)
/MISO: J8.2, U4.2 (PB6)
/MOSI: J8.3, U4.1 (PB5)
/RESET: J11.1, R5.2, U4.4 (~RESET)
/Reverse_Latch: J14.1, R11.2, U4.21 (PC2)
/Reverse_PWM: J15.1, R12.1, U4.22 (PC3)
/SCK: J8.1, U4.3 (PB7)
/Servo 5V: J6.2, J17.1
/Servo Sig: J6.1, U4.13 (PD4)
/U1-Reset: R3.2, SW1.2 (B), U1.1 (RESET), U2.1 (EN), U3.3 (EN)
/U1-VDD: C2.1, R1.2, R2.1, U1.2 (VDD)
GND: C6.2, C7.2, C8.2, C9.2, D4.2 (A), D5.2 (A), J4.2, J5.2, J6.3, J7.1, J16.1, Q1.2 (E), Q4.2 (E), Q5.2 (S), Q6.2 (S), R7.2, R10.2, R13.2, R14.2, U4.6 (GND), U4.18 (GND), U4.28 (GND), U4.39 (GND)
GND Main: C1.2, C2.2, C3.2, C4.2, C5.2, D1.1 (K), J1.2, J3.1, R2.2, SW1.1 (A), U1.3 (GND), U2.5 (GND), U2.6 (GND), U2.7 (GND), U2.8 (GND), U3.2 (GND)
unnamed: D1.2 (A), R4.1
unnamed: D2.2 (A), D4.1 (K), M+1.1, Q2.3 (D), Q5.3 (D)
unnamed: D3.2 (A), D5.1 (K), M-1.1, Q3.3 (D), Q6.3 (D)
unnamed: Q1.1 (B), R6.2, R7.1
unnamed: Q1.3 (C), Q2.1 (G), R8.2
unnamed: Q3.1 (G), Q4.3 (C), R9.2
unnamed: Q4.1 (B), R10.1, R11.1
unnamed: Q5.1 (G), R12.2, R13.1
unnamed: Q6.1 (G), R14.1, R15.1

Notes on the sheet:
H-Bridge Motor Driver (Board 2)
8.4V Headers
Test Points
nRF24L01+ Headers
Test Point
3.3V Headers
ATmega164A Control Unit (Board 2)
Power Management & Regulation (Board 1)
Servo Motor Headers

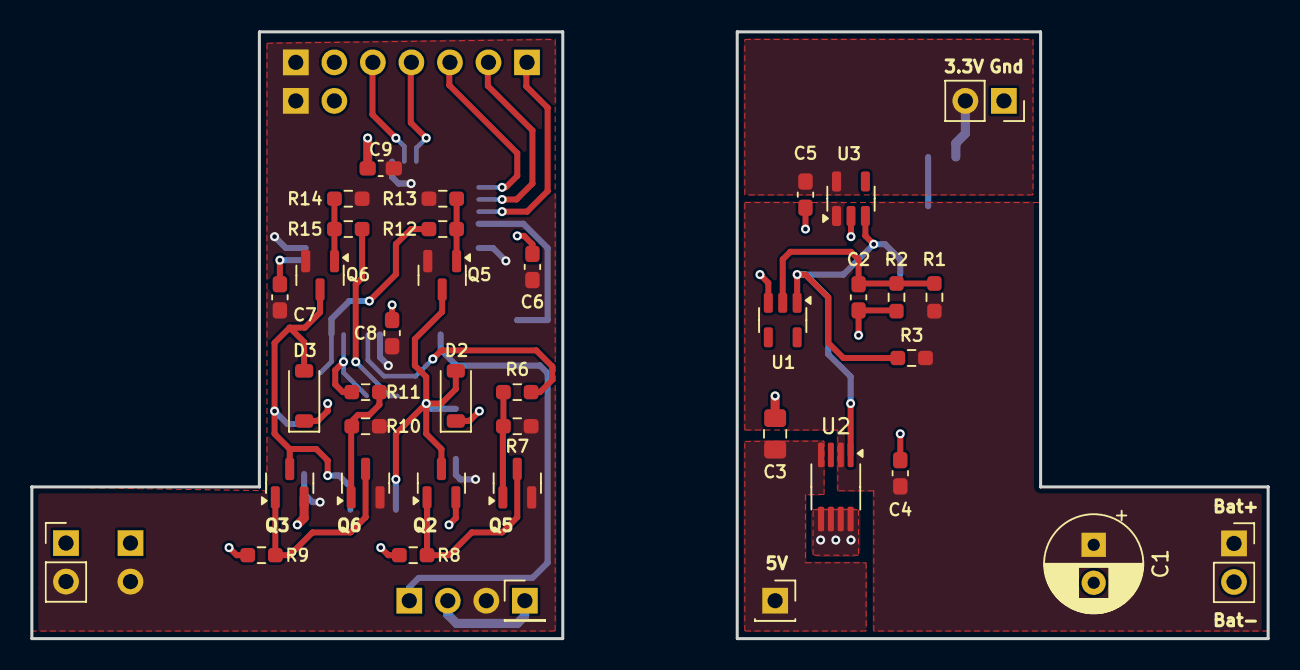
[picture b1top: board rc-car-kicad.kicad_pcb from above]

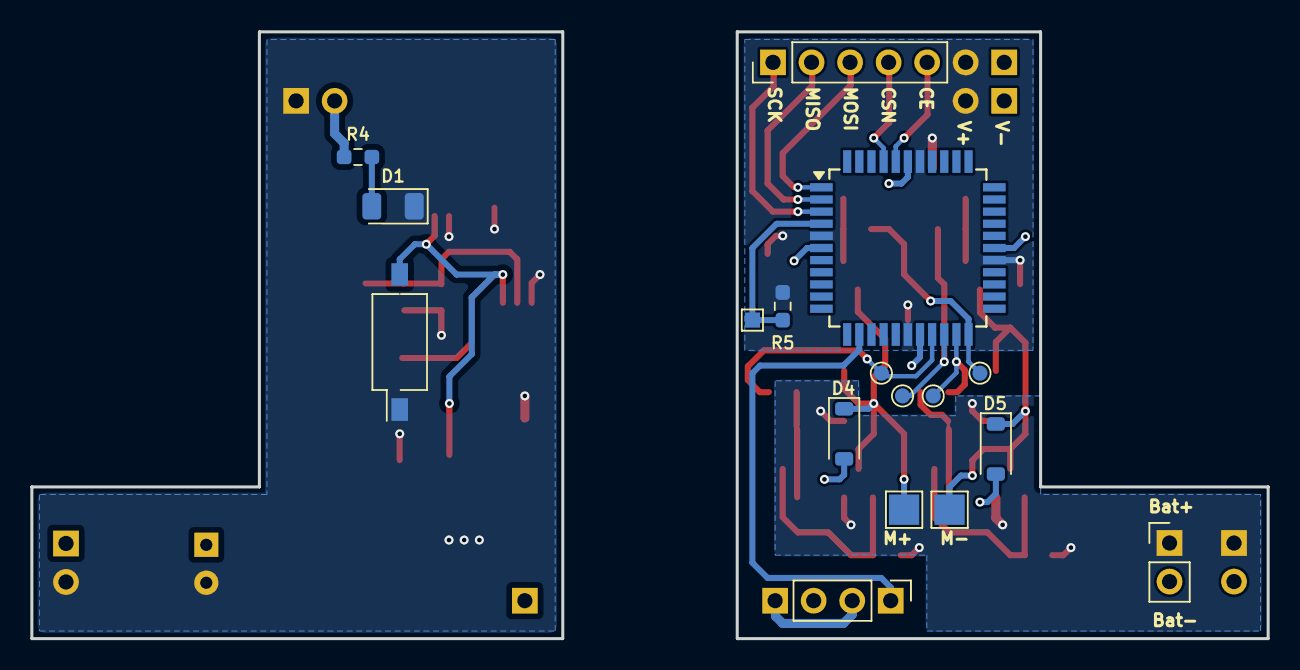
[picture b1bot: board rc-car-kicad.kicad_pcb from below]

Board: 2 copper layers, 81.5 x 40.0 mm, 57 parts (18 on the bottom side), 30 nets.

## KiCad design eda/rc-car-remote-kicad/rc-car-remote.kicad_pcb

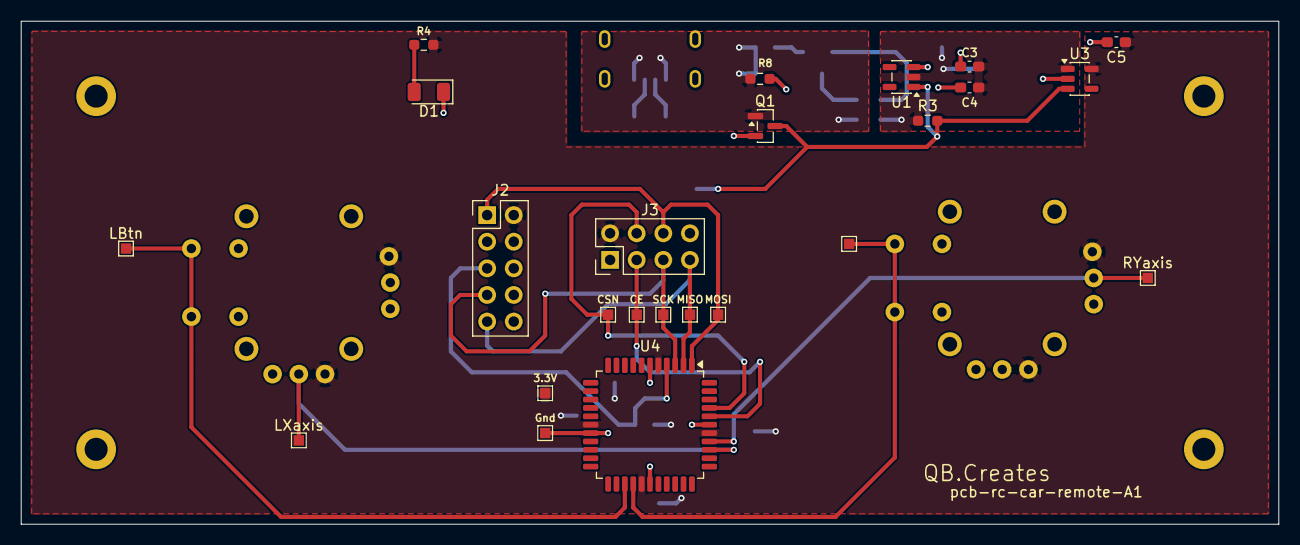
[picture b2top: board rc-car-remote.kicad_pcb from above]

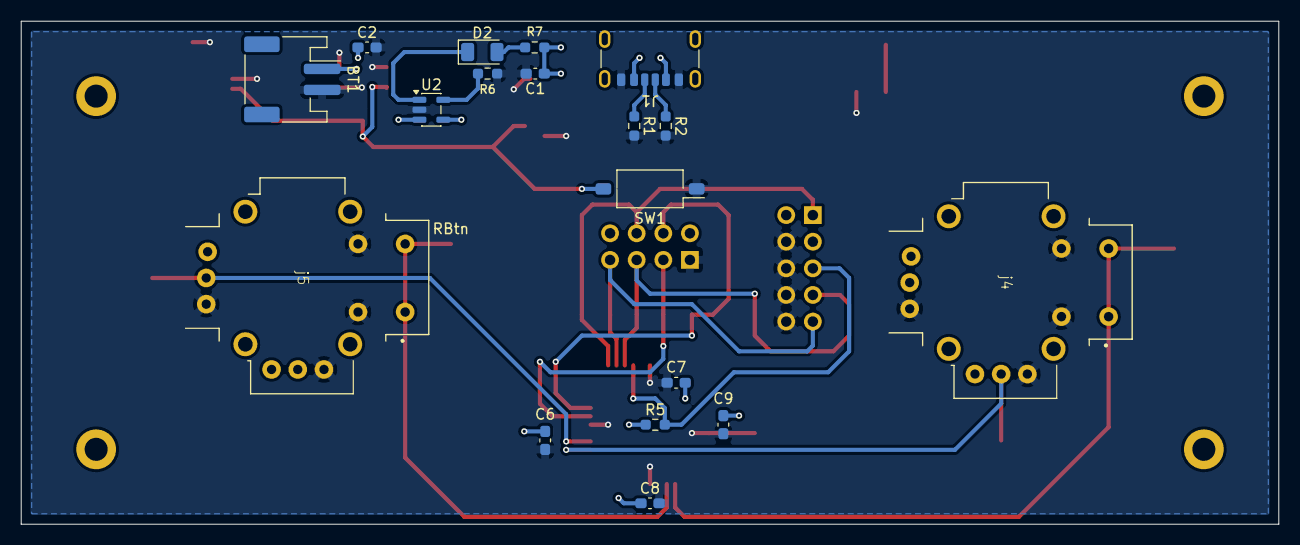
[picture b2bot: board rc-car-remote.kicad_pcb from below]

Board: 2 copper layers, 120.0 x 48.0 mm, 42 parts (18 on the bottom side), 21 nets.

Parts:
3.3V: 3.3V; TestPoint_Pad_1.0x1.0mm
BT1: 4.2V Lipo; JST_PH_S2B-PH-SM4-TB_1x02-1MP_P2.00mm_Horizontal
C1, C2: 4.7uF; C_0603_1608Metric_Pad1.08x0.95mm_HandSolder
C3, C4: 1uF; C_0603_1608Metric_Pad1.08x0.95mm_HandSolder
C5: 2.2uF; C_0603_1608Metric_Pad1.08x0.95mm_HandSolder
C6, C7, C8, C9: .1uF; C_0603_1608Metric_Pad1.08x0.95mm_HandSolder
CE: CE; TestPoint_Pad_1.0x1.0mm
CSN: CSN; TestPoint_Pad_1.0x1.0mm
D1, D2: LED; LED_1206_3216Metric
Gnd: Gnd; TestPoint_Pad_1.0x1.0mm
J1: USB_C_Receptacle_USB2.0_14P; USB_C_Receptacle_GCT_USB4125-xx-x-0190_6P_TopMnt_Horizontal
J2: AVR-ISP-10; PinHeader_2x05_P2.54mm_Vertical
J3: nRF24L01+ Headers; PinHeader_2x04_P2.54mm_Vertical
LBtn: LBtn; TestPoint_Pad_1.0x1.0mm
LXaxis: LXaxis; TestPoint_Pad_1.0x1.0mm
MISO: MISO; TestPoint_Pad_1.0x1.0mm
MOSI: MOSI; TestPoint_Pad_1.0x1.0mm
Q1: IRLML6244; SOT-23
R1, R2: 5.1k; R_0603_1608Metric_Pad0.98x0.95mm_HandSolder
R3: 150k; R_0603_1608Metric_Pad0.98x0.95mm_HandSolder
R4: 1.5k; R_0603_1608Metric_Pad0.98x0.95mm_HandSolder
R5, R6: 10k; R_0603_1608Metric_Pad0.98x0.95mm_HandSolder
R7: 330; R_0603_1608Metric_Pad0.98x0.95mm_HandSolder
R8: 1.3k; R_0603_1608Metric_Pad0.98x0.95mm_HandSolder
RBtn: RBtn; TestPoint_Pad_1.0x1.0mm
RYaxis: RYaxis; TestPoint_Pad_1.0x1.0mm
SCK: SCK; TestPoint_Pad_1.0x1.0mm
SW1: SW_SPST; SW_DIP_SPSTx01_Slide_Omron_A6S-110x_W8.9mm_P2.54mm
U1: TPS3840; SOT-23-5
U2: MCP73831-2-OT; SOT-23-5
U3: MIC5225-3.3YM5; SOT-23-5
U4: ATmega164A-A; TQFP-44_10x10mm_P0.8mm
j4, j5: B09Y2R1GLV; Jao B09Y2R1GLV

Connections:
+3.3V Main: 3.3V.1 (Pin_1_1), C5.1, C6.1, C7.1, C8.1, C9.1, J2.2 (VCC), J3.2, R4.2, R5.1, U3.5 (OUT), U4.5 (VCC), U4.17 (VCC), U4.27 (AVCC), U4.38 (VCC), j4.1 (V), j5.1 (V)
/4.2V Bat: BT1.1 (+), C2.1, C3.1, C4.1, R3.1, U1.2 (VDD), U2.3 (V_{BAT}), U3.1 (IN)
/5V USB: C1.1, J1.A9 (VBUS), J1.B9 (VBUS), Q1.1 (G), R7.1, R8.1, U2.4 (V_{DD})
/CE: CE.1 (Pin_1_1), J3.3, U4.40 (PB0)
/CSN: CSN.1 (Pin_1_1), J3.4, U4.41 (PB1)
/LBtn: LBtn.1 (Pin_1_1), U4.25 (PC6), j4.5 (SEL+)
/LXaxis: LXaxis.1 (Pin_1_1), U4.36 (PA1), j4.3 (VRX)
/MISO: J2.9 (MISO), J3.7, MISO.1 (Pin_1_1), U4.2 (PB6)
/MOSI: J2.1 (MOSI), J3.6, MOSI.1 (Pin_1_1), U4.1 (PB5)
/RBtn: RBtn.1 (Pin_1_1), U4.26 (PC7), j5.5 (SEL+)
/RESET: J2.5 (~RST), R5.2, U4.4 (~RESET)
/RYaxis: RYaxis.1 (Pin_1_1), U4.37 (PA0), j5.4 (VRY)
/SCK: J2.7 (SCK), J3.5, SCK.1 (Pin_1_1), U4.3 (PB7)
/U1-Reset: Q1.3 (D), R3.2, SW1.2 (B), U1.1 (RESET), U3.3 (EN)
GNDREF: BT1.2 (-), C1.2, C2.2, C3.2, C4.2, C5.2, C6.2, C7.2, C8.2, C9.2, D1.1 (K), Gnd.1 (Pin_1_1), J1.A12 (GND), J1.B12 (GND), J2.4 (GND), J2.6 (GND), J2.8 (GND), J2.10 (GND), J3.1, Q1.2 (S), R1.2, R2.2, R6.2, R8.2, SW1.1 (A), U1.3 (GND), U2.2 (V_{SS}), U3.2 (GND), U4.6 (GND), U4.18 (GND), U4.28 (GND), U4.39 (GND), j4.2 (Gnd), j4.6 (SEL-), j5.2 (Gnd), j5.6 (SEL-)
unnamed: D1.2 (A), R4.1
unnamed: D2.2 (A), R7.2
unnamed: D2.1 (K), U2.1 (STAT)
unnamed: J1.A5 (CC1), R2.1
unnamed: J1.B5 (CC2), R1.1
unnamed: R6.1, U2.5 (PROG)

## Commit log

2025-08-17 Update .gitignore
    Updated the gitignor to account for platform.io files
2025-08-18 - Adding the rc motor controls project to the repo - Adding the rc car remote control project to the repo
2025-08-24 - Uploading Kicad project - Change delay for shutting off the motor to 500 ms
2025-08-24 - Added new pcb schmatic with a panel that contains boath circuit boards
2025-08-26 - Updated the panel pcb and schematic - Added a boost functionality - Removed unnecessary usart code - Movied analog reading code into the joystick class
2025-08-27 - Reduced the delay time when changing directions to 150 ms - made our deadzone between the values -15 and 15 - Configured the wdt to reset only if data has already been and if data hasnt been receiv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
2025-08-28 - Moved the rc car and rc car controller into a software directory
2025-09-06 - Redesigned power portion of the pcb - Changed the board to atmega164A
2025-09-06 - Made improvements to power and ground plains on the powere pcb - Updated the component labels in the schematic
2025-09-07 - Updated the microcontroller pcb
2025-09-07 - Added testing points for H-Bridge connections to the PCB
2025-09-07 - Modified the header pins a bit on the pcb
2025-09-08 - Updated panelized board. Fixed all design route errors
2025-09-09 - Documented the schematic and created a pdf of the schematic
2025-09-10 - Added an images directory with images of the pcb and the schematic - Added a revision number to the pcb. - Finalized pcb and schematic
2026-04-20 - Added code docs to all cpp files - Remved boost code - Removed commented code - Clamped the steering values to be 1200 - 1700
2026-04-20 - Adding new images. - Adding temp readme
2026-04-20 - updated the readme to have more relevant sections
2026-05-04 Adding rc-car-remote kicad project to the repo
2026-05-04 - Adding example readme - Adding temp readme - Adding alterante address for bmw vs jaguar - Changed the speed range to be from -190 to 190 - Updated the min and max values for steering - Fixed commen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
2026-05-15 - Made the steering motor center 1780 - added stl for car parts
2026-05-15 - updated the parts list for the remote and the car
2026-05-15 Updated the parts list
2026-05-15 Added section for power cunsumption and schematics
2026-05-15 - Added an stlviewer sectino to the read me
2026-05-18 - Added images for all circuits - changed the remote control microcontroller target to an atmega164A
2026-05-18 - renamed rc-car-atmega164A to rc-car - renamed rc-car-remote-atmega1284 to rc-car-remote
2026-05-18 - renamed the software folders to rc-transmitter-firmware and drive-and-steering-control-firmware
2026-05-18 - Added new images and placed them in the readme
2026-05-18 - add the steering sevo control and drive motor control sections
2026-05-19 - Updated project folder names
2026-05-19 - updated the readme
2026-05-19 - Updated read me
2026-05-20 - Added stl for controller to readme
2026-05-20 - adding other stl
2026-05-20 - Updated stl
2026-05-20 testing stl
2026-05-20 - reuploading stl
2026-05-20 - Trying New stl
2026-05-20 - new stl
2026-05-20 - Rc car parts stls
2026-05-21 - stl upload attempt again
2026-05-21 - One more upload
2026-05-21 - One more try
2026-05-21 - Motor Mount stls
2026-05-21 more car parts stl
2026-05-21 - The rest of the car parts stl
2026-05-22 - updated read,e
2026-05-23 - added video demonstration link and microcontroller input mapping to the readme
2026-05-24 - Uploading rc car remote gerber files - Updated the 3d models for the rc car circuit. Changed them all to .step
2026-05-24 - Updated the 3d image of the rc car remote circuit

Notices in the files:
README.md:
License:
See [LICENSE](LICENSE) for details.
